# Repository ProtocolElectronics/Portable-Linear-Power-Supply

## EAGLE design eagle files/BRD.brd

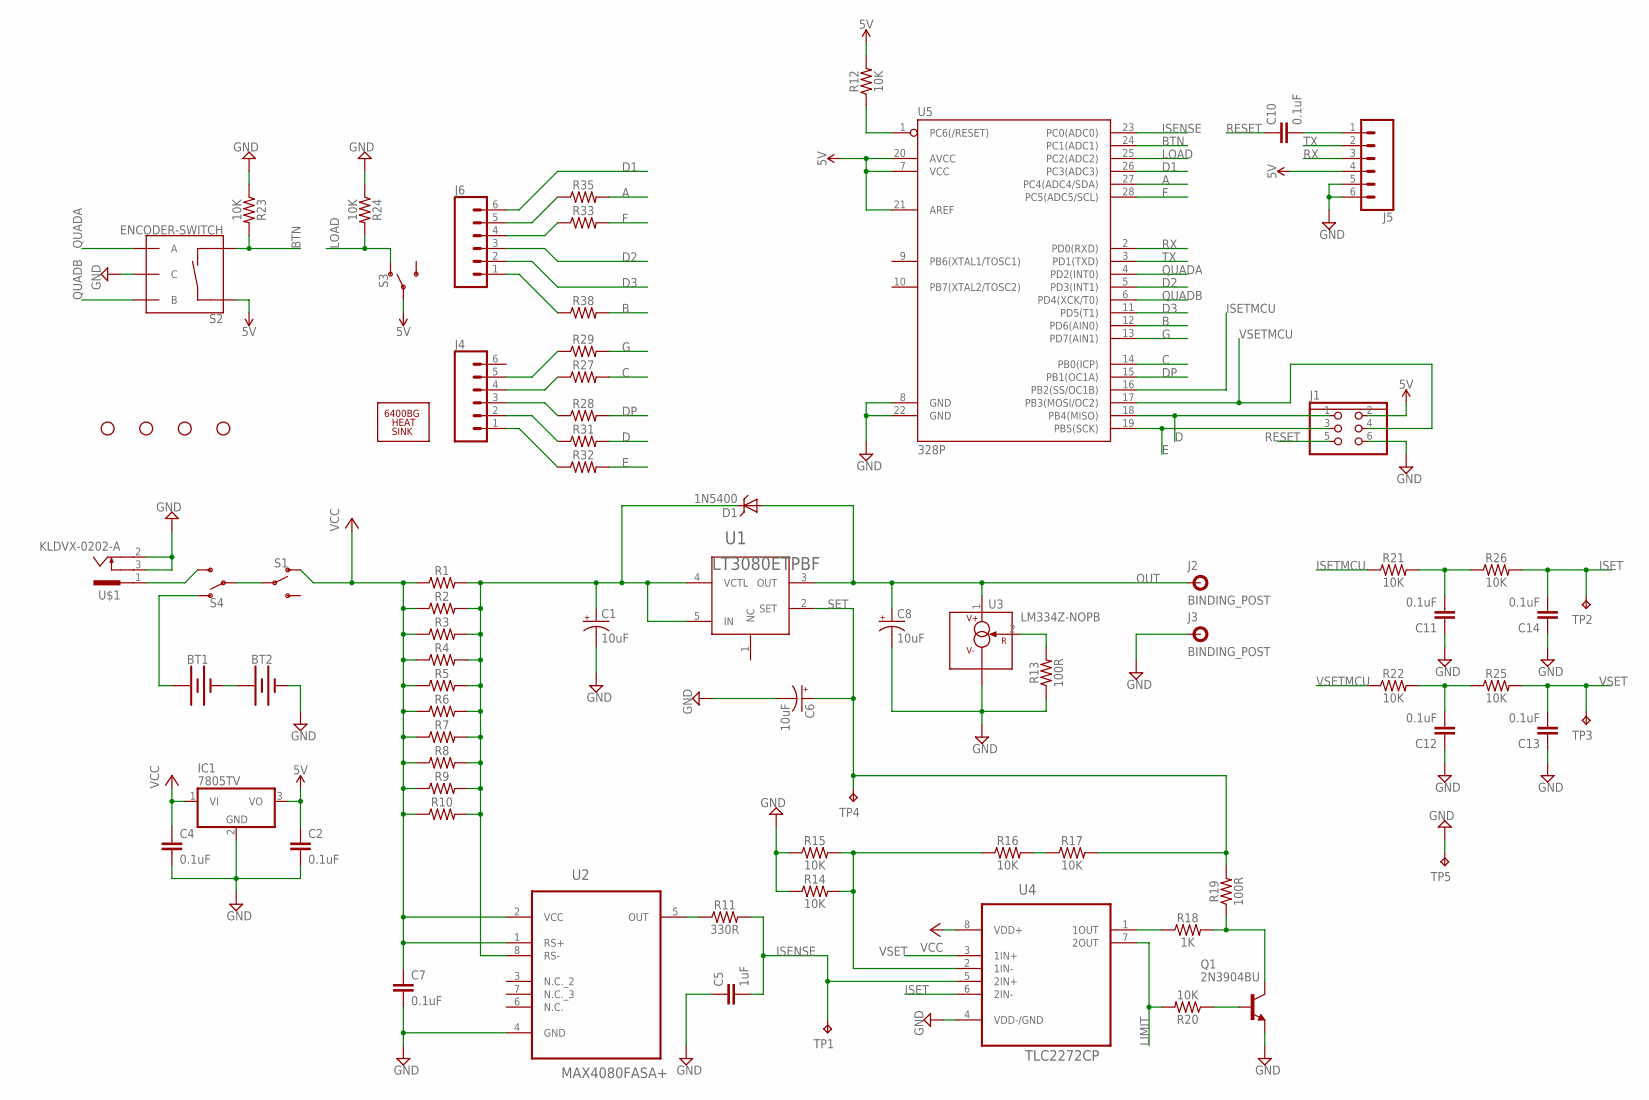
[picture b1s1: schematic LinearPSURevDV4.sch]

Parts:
BT1, BT2: BATTERY-9V; BATTCON_9V
C1, C6, C8: 10uF; CPOL-RADIAL-2.5MM-5MM
C2, C4, C7, C10, C11, C12, C13, C14: 0.1uF; CAP-PTH-2.54
C5: 1uF; CAP-PTH-2.54
D1: 1N5400; DO201-15
H1, H2, H3, H4: STAND-OFF
H5: 6400BG_HEATSINK
IC1: 7805TV; TO220V
J1: PINHD2X03
J2, J3: BINDING_POST
J4, J5, J6: CONN_06NO_SILK_FEMALE_PTH; 1X06_NO_SILK
Q1: 2N3904BU; TO92
R1, R2, R3, R4, R5, R6, R7, R8, R9, R10: 2R; 0603
R11: 330R; AXIAL-0.3
R12, R14, R15, R16, R17, R20, R21, R22, R23, R24, R25, R26, R27, R28, R29, R31, R32, R33, R35, R38: 10K; AXIAL-0.3
R13, R19: 100R; AXIAL-0.3
R18: 1K; AXIAL-0.3
S1, S3, S4: SWITCH-SPDT-PTH-11.6X4.0MM-LOCK; SWITCH_SPDT_PTH_11.6X4.0MM_LOCK
S2: ENCODER-SWITCH; ROTARY_ENC_PLAIN
TP1, TP2, TP3, TP4, TP5: TPTP14SQ; TP14SQ
U1: LT3080ETPBF; TO220-51
U2: MAX4080FASA+; SOIC127P600X175-8N
U3: LM334Z-NOPB; TO92
U4: TLC2272CP; DIP254P762X508-8
U5: 328P; DIP28
U$1: KLDVX-0202-A

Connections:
5V: C2.1, IC1.3 (VO), J1.2, J5.4, R12.P$2 (2), S2.SW+, S3.2, U5.7 (VCC), U5.20 (AVCC), U5.21 (AREF)
A: R35.P$2 (2), U5.27 (PC4(ADC4/SDA))
B: R38.P$2 (2), U5.12 (PD6(AIN0))
BTN: R23.P$2 (2), S2.SW-, U5.24 (PC1(ADC1))
C: R27.P$2 (2), U5.14 (PB0(ICP))
D: J1.1, R31.P$2 (2), U5.18 (PB4(MISO))
D1: J6.6, U5.26 (PC3(ADC3))
D2: J6.3, U5.5 (PD3(INT1))
D3: J6.2, U5.11 (PD5(T1))
DP: R28.P$2 (2), U5.15 (PB1(OC1A))
E: J1.3, R32.P$2 (2), U5.19 (PB5(SCK))
F: R33.P$2 (2), U5.28 (PC5(ADC5/SCL))
G: R29.P$2 (2), U5.13 (PD7(AIN1))
GND: BT2.-, C1.2 (-), C2.2, C4.2, C5.1, C6.2 (-), C7.2, C8.2 (-), C11.1, C12.1, C13.1, C14.1, IC1.2 (GND), J1.6, J3.P$1, J5.5, J5.6, Q1.3 (E), R13.P$1 (1), R14.P$1 (1), R15.P$1 (1), R23.P$1 (1), R24.P$1 (1), S2.C, TP5.TP, U2.4 (GND), U3.3 (V-), U4.4 (VDD-/GND), U5.8 (GND), U5.22 (GND), U$1.2, U$1.3
ISENSE: C5.2, R11.P$2 (2), TP1.TP, U4.5 (2IN+), U5.23 (PC0(ADC0))
ISET: C14.2, R26.P$2 (2), TP2.TP, U4.6 (2IN-)
ISETMCU: R21.P$1 (1), U5.16 (PB2(SS/OC1B))
LIMIT: R20.P$2 (2), U4.7 (2OUT)
LOAD: R24.P$2 (2), S3.1 (O), U5.25 (PC2(ADC2))
unnamed: S4.3 (S), U$1.1
unnamed: C10.2, J5.1
unnamed: C1.1 (+), D1.C, R1.2, R2.2, R3.2, R4.2, R5.2, R6.2, R7.2, R8.2, R9.2, R10.2, U1.4 (VCTL), U1.5 (IN), U2.8 (RS-)
unnamed: R11.P$1 (1), U2.5 (OUT)
unnamed: R18.P$1 (1), U4.1 (1OUT)
unnamed: R13.P$2 (2), U3.2 (R)
unnamed: Q1.1 (C), R18.P$2 (2), R19.P$1 (1)
unnamed: Q1.2 (B), R20.P$1 (1)
unnamed: R16.P$2 (2), R17.P$1 (1)
unnamed: R14.P$2 (2), R15.P$2 (2), R16.P$1 (1), U4.2 (1IN-)
unnamed: BT1.-, BT2.+
unnamed: S1.2, S4.2
unnamed: BT1.+, S4.1 (O)
unnamed: J4.5, R29.P$1 (1)
unnamed: J4.4, R27.P$1 (1)
unnamed: J4.3, R28.P$1 (1)
unnamed: C11.2, R21.P$2 (2), R26.P$1 (1)
unnamed: C12.2, R22.P$2 (2), R25.P$1 (1)
unnamed: J4.2, R31.P$1 (1)
unnamed: J4.1, R32.P$1 (1)
unnamed: J6.5, R35.P$1 (1)
unnamed: J6.4, R33.P$1 (1)
unnamed: J6.1, R38.P$1 (1)
OUT: C8.1 (+), D1.A, J2.P$1, U1.3 (OUT), U3.1 (V+)
QUADA: S2.A, U5.4 (PD2(INT0))
QUADB: S2.B, U5.6 (PD4(XCK/T0))
RESET: C10.1, J1.5, R12.P$1 (1), U5.1 (PC6(/RESET))
RX: J5.3, U5.2 (PD0(RXD))
SET: C6.1 (+), R17.P$2 (2), R19.P$2 (2), TP4.TP, U1.2 (SET)
TX: J5.2, U5.3 (PD1(TXD))
VCC: C4.1, C7.1, IC1.1 (VI), R1.1, R2.1, R3.1, R4.1, R5.1, R6.1, R7.1, R8.1, R9.1, R10.1, S1.1 (O), U2.1 (RS+), U2.2 (VCC), U4.8 (VDD+)
VSET: C13.2, R25.P$2 (2), TP3.TP, U4.3 (1IN+)
VSETMCU: J1.4, R22.P$1 (1), U5.17 (PB3(MOSI/OC2))

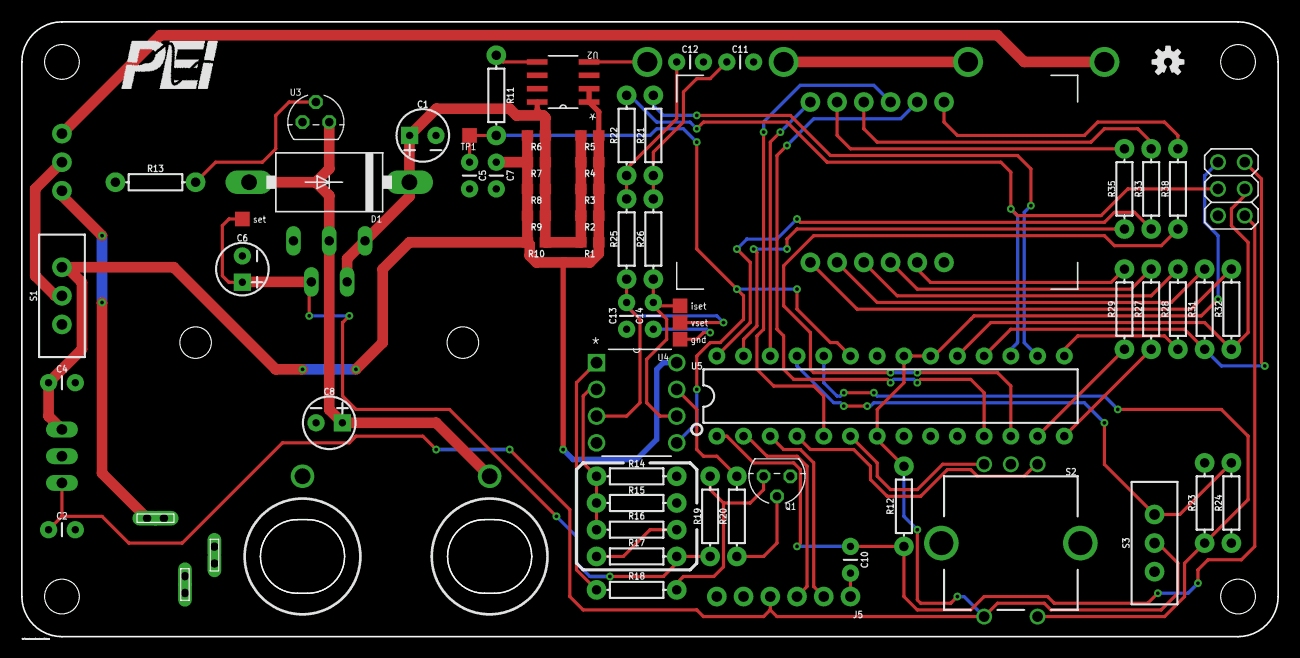
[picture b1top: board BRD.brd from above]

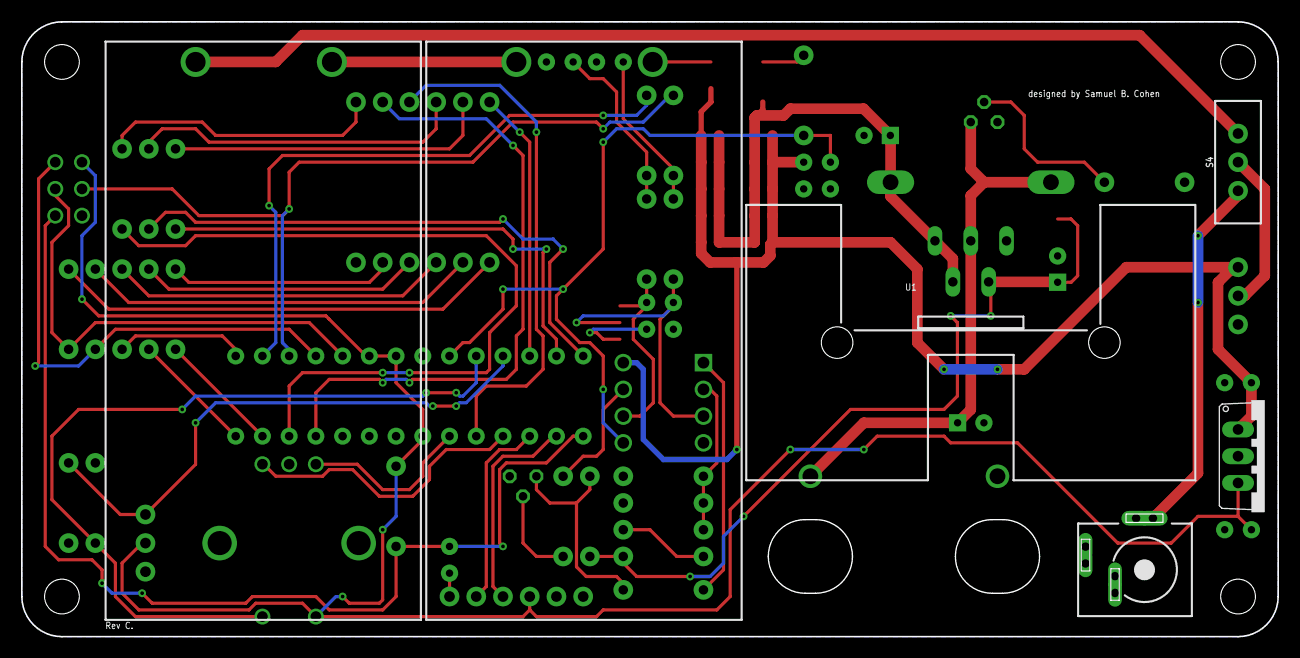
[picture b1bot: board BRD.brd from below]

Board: 2 copper layers, 119.4 x 58.4 mm, 78 parts (7 on the bottom side), 52 nets.

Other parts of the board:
U$2: OSHW-LOGO-S

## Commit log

2017-07-22 add images
2017-07-22 add eagle files
2017-07-23 change directory structure
2017-07-25 add assembly instructions
2017-07-25 add operation instructions
2017-07-28 add BOM and License information
2017-07-28 small fix with md

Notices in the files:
parts and their libraries:
SparkFun-Batteries: Licensing: Creative Commons ShareAlike 4.0 International - https://creativecommons.org/licenses/by-sa/4.0
